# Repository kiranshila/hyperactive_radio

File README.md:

# Hyperactive//2026 Radio

Experimental real-time, long-range, high-quality, wireless digital audio for Hyperactive 2026.

## Audio quality

| Parameter | Value |
|-----------|-------|
| Codec | Opus (fixed-point) |
| Bitrate | 64 kbps |
| Channels | Stereo |
| Sample rate | 48 kHz |
| Frame size | 20 ms |
| Encoder complexity | 5 / 10 |
| ADC | PCM1808 (24-bit I2S) |

64 kbps stereo Opus at 48 kHz should be transparent for most program material — comparable to a good 128 kbps MP3, but with lower latency and better behaviour at the edges of the bitrate.
The fixed-point build removes float entirely; no performance penalty on Cortex-M33 which has a hardware FPU but where the float Opus path was benchmarked to be slower than fixed-point.

End-to-end latency is approximately one frame (20 ms) of algorithmic delay plus radio airtime (~1.6 ms at 100 kbps for a 160-byte packet) plus any playout buffer on the receiver.

## Radio

| Parameter | Value |
|-----------|-------|
| Radio IC | SX1276 |
| Band | 915 MHz (US ISM) |
| Modulation | GFSK |
| Air rate | 100 kbps |
| TX power | +20 dBm (100 mW) |
| Target range | ~300 m / ~1000 ft mixed indoor/outdoor |
| Link margin | ~18 dB at 100 kbps GFSK |

### Regulatory (FCC Part 15.247)

No frequency hopping required. Part 15.247 has two compliance paths — FHSS is one, but **digital modulation** is the other: fixed frequency, up to +30 dBm EIRP, with two constraints:

- **6 dB bandwidth ≥ 500 kHz** — requires high frequency deviation; at 100 kbps, ±200 kHz deviation gets you there (`BW_6dB ≈ 2 × f_dev + bit_rate`). Lower deviation (e.g. ±50 kHz) only yields ~200 kHz and does not qualify.
- **PSD ≤ 8 dBm in any 3 kHz band** — GFSK spectral peaks at ±f_dev must stay under this limit at the chosen TX power.

The exact deviation and power settings need to be verified against both constraints once the RF configuration is finalised. At +20 dBm with sufficiently high deviation the path is viable, but the numbers need to be checked.

### Packet structure

Each 20 ms Opus frame encodes to roughly 160 bytes at 64 kbps.
With ~10 bytes of framing (sequence number, network ID, CRC) the total packet is ~170 bytes, for an effective air rate of ~68 kbps — well within the 100 kbps channel.

## Performance

MCU runs at **270 MHz** (overclocked from the 150 MHz default; stable at stock 1.1 V).

Benchmarked on hardware against broadband LCG noise (worst case for Opus — no clear pitch, flat spectrum):

| Operation | Cycles (avg) | Time (avg) | Frame budget used |
|-----------|-------------|------------|-------------------|
| Opus encode, stereo, 64 kbps, 20 ms | 2,299,603 | 8.5 ms | **42.6%** |
| Opus decode, stereo, 64 kbps, 20 ms | 895,420 | 3.3 ms | **16.6%** |

Frame budget = 20 ms = 5,400,000 cycles at 270 MHz.

The encoder leaves 11.5 ms of headroom per frame for I2S DMA and SPI radio management.
The decoder uses only 16.6% of the frame, leaving ample margin for playout buffering and output DMA.

## Firmware architecture

Written in Rust (`no_std`, Embassy async runtime).

```
ha_radio/          # firmware binary (bench + main)
embedded-opus/     # safe Rust wrapper around libopus
opus-sys/          # raw FFI bindings; builds libopus via cc crate
```

`embedded-opus/build.rs` compiles a host-side C probe at build time to determine the exact encoder and decoder state sizes, so buffers are sized precisely without a runtime heap.

### Planned: dual-core pipeline

The encode headroom is comfortable at 270 MHz, but the dual-core split is still planned for clean separation of concerns once the ADC arrives:

- **Core 0** — I2S DMA capture, SX1276 SPI, radio management
- **Core 1** — Opus encode only

A pair of Embassy `Channel` queues (depth 2) connect the cores: PCM frames inbound, encoded packets outbound.

## Build

```sh
cargo build --release --bin ha_radio
cargo build --release --bin bench
```

Requires a Rust nightly toolchain and the `thumbv8m.main-none-eabihf` target (see `rust-toolchain.toml`).

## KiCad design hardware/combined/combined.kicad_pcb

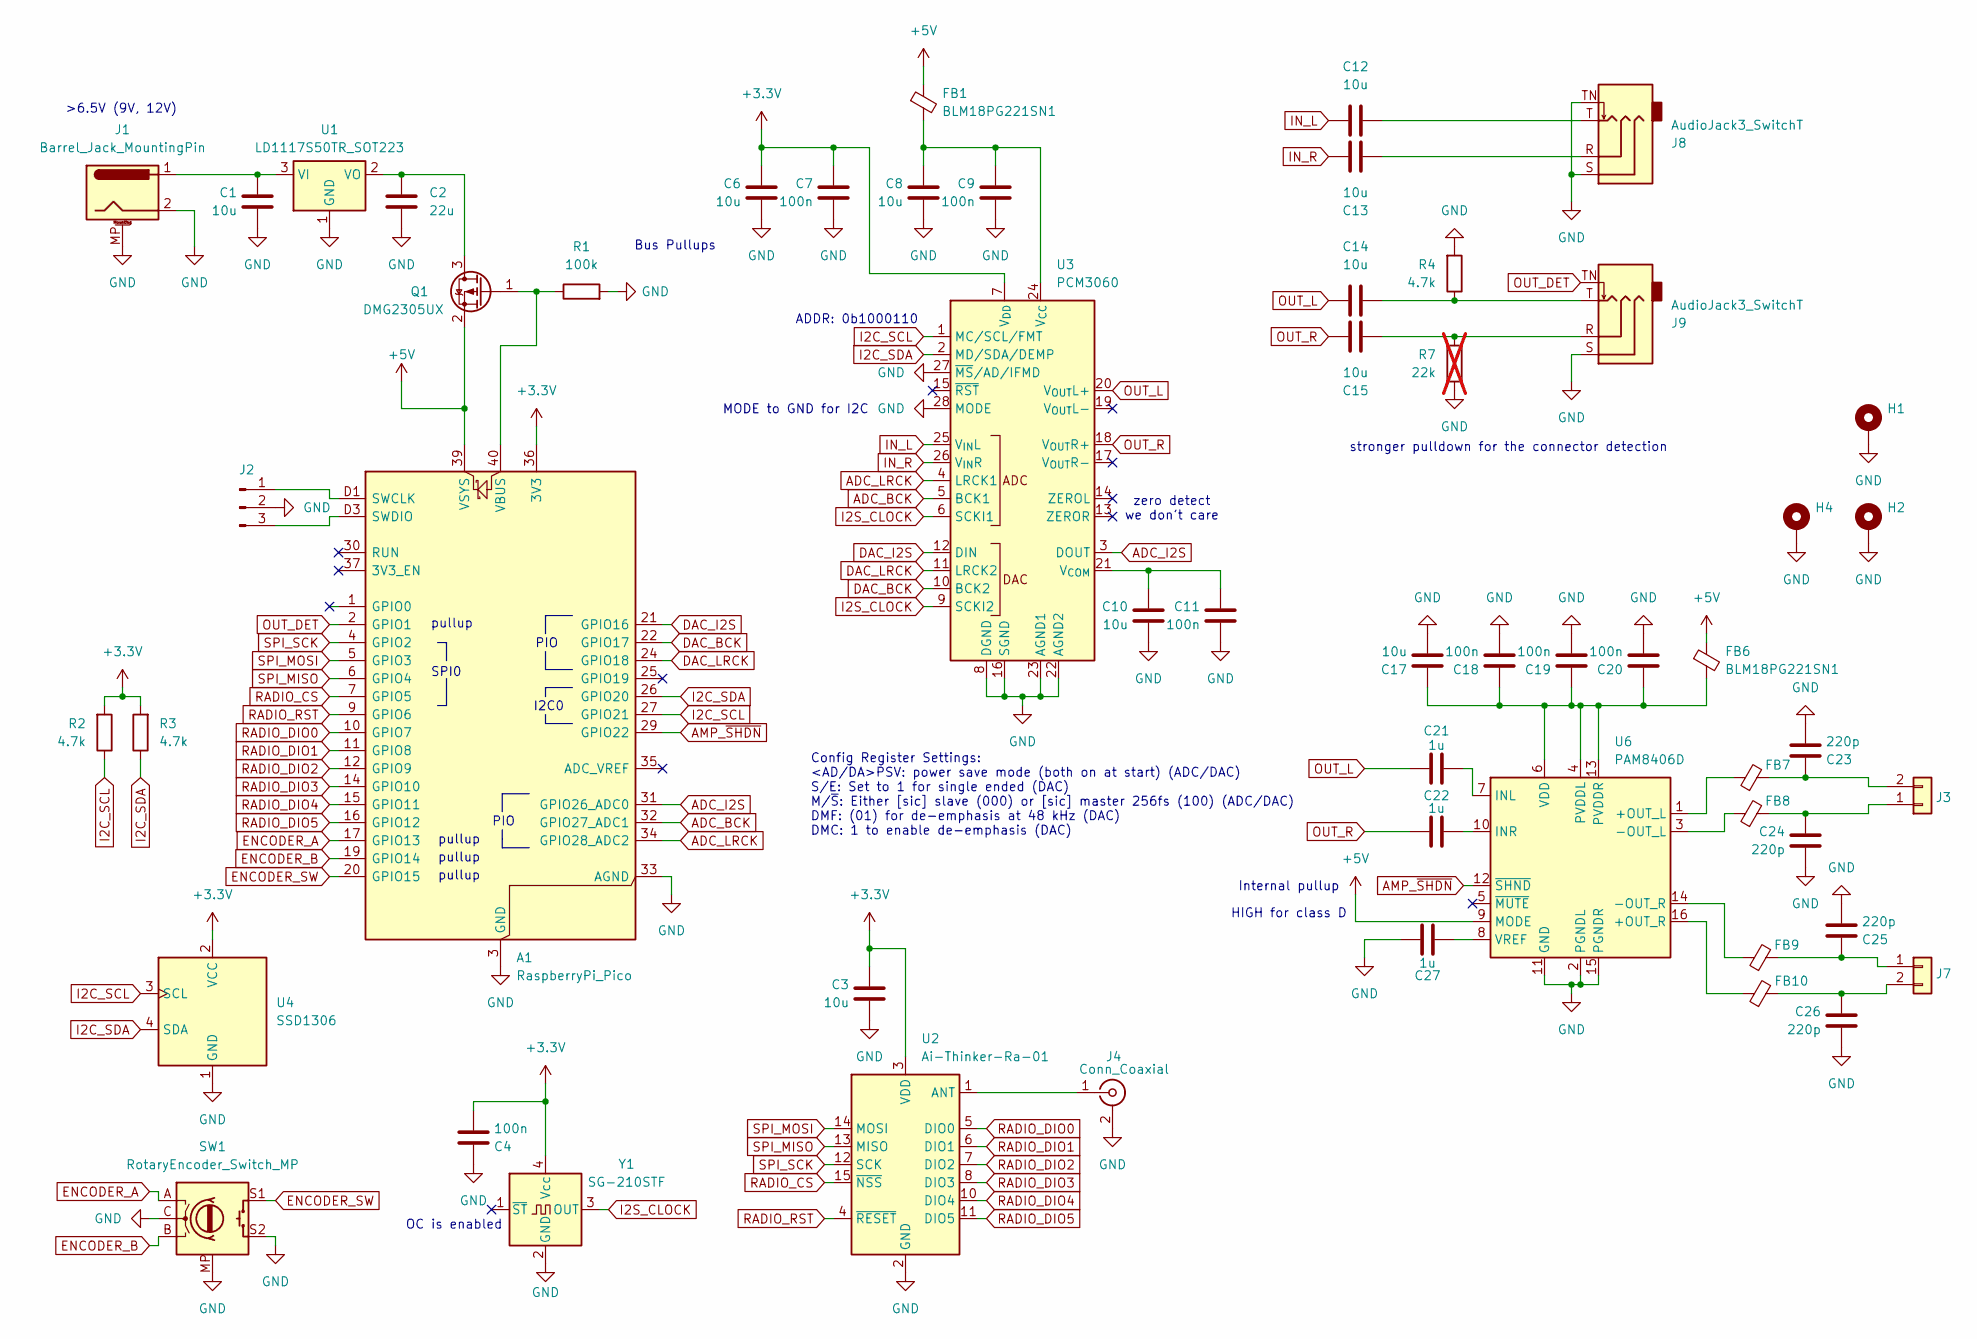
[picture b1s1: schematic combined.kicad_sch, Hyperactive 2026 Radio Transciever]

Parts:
A1: RaspberryPi_Pico; RaspberryPi_Pico_SMD_HandSolder; LCSC C41407547
C1, C3, C6, C8, C10, C12, C13, C14, C15, C17: 10u; C_0805_2012Metric; MPN CL21A106KOQNNNG
C2: 22u; C_0805_2012Metric; MPN GRM21BR61A226ME51L
C4, C7, C9, C11, C18, C19, C20: 100n; C_0805_2012Metric; MPN 0805ZD104KAT2A
C21, C22, C27: 1u; C_0805_2012Metric; MPN 0805X105K160CT
C23, C24, C25, C26: 220p; C_0603_1608Metric; MPN C0603C221J1HACAUTO
FB1, FB6, FB7, FB8, FB9, FB10: BLM18PG221SN1; L_0603_1608Metric; MPN BLM18PG221SN1; LCSC C80165
H1, H2, H4: MountingHole_Pad; MountingHole_3.2mm_M3_DIN965_Pad_TopBottom
J1: Barrel_Jack_MountingPin; BarrelJack_Horizontal
J2: Conn_01x03_Pin; PinHeader_1x03_P2.54mm_Vertical
J3, J7: Conn_01x02; PinHeader_1x02_P2.54mm_Vertical
J4: Conn_Coaxial; SMA_Samtec_SMA-J-P-H-ST-EM1_EdgeMount; LCSC C496550
J8, J9: AudioJack3_SwitchT; Jack_3.5mm_CUI_SJ-3524-SMT_Horizontal; MPN SJ-3524-SMT-TR; LCSC C20182907
Q1: DMG2305UX; SOT-23; LCSC C150470
R1: 100k; R_0805_2012Metric; MPN RG2012P-104-B-T5
R2, R3, R4: 4.7k; R_0805_2012Metric; MPN RG2012P-472-D-T5
R7: 22k; R_0805_2012Metric; MPN RG2012P-223-B-T5; not fitted
SW1: RotaryEncoder_Switch_MP; RotaryEncoder_Alps_EC11E-Switch_Vertical_H20mm; MPN EC11E09244BS; LCSC C470742
U1: LD1117S50TR_SOT223; SOT-223-3_TabPin2; LCSC C347230
U2: Ai-Thinker-Ra-01; Ai-Thinker-Ra-01-LoRa; LCSC C503593
U3: PCM3060; TSSOP-28_4.4x9.7mm_P0.65mm; MPN PCM3060PWR; LCSC C2651841
U4: SSD1306; SSD1306_0.96_Oled
U6: PAM8406D; SOIC-16_3.9x9.9mm_P1.27mm; MPN PAM8406DR; LCSC C86270
Y1: SG-210STF; Oscillator_SMD_SeikoEpson_SG210-4Pin_2.5x2.0mm; MPN X1G0041710019; LCSC C255992

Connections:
+3.3V: A1.36 (3V3), C3.2, C4.1, C6.2, C7.2, R2.2, R3.2, U2.3 (VDD), U3.7 (V_{DD}), U4.2 (VCC), Y1.4 (Vcc)
+5V: A1.39 (VSYS), FB1.1, FB6.1, Q1.2 (S), U6.9 (MODE)
ADC_BCK: A1.32 (GPIO27_ADC1), U3.5 (BCK1)
ADC_I2S: A1.31 (GPIO26_ADC0), U3.3 (DOUT)
ADC_LRCK: A1.34 (GPIO28_ADC2), U3.4 (LRCK1)
AMP_~SHDN: A1.29 (GPIO22), U6.12 (~SHND)
DAC_BCK: A1.22 (GPIO17), U3.10 (BCK2)
DAC_I2S: A1.21 (GPIO16), U3.12 (DIN)
DAC_LRCK: A1.24 (GPIO18), U3.11 (LRCK2)
ENCODER_A: A1.17 (GPIO13), SW1.A
ENCODER_B: A1.19 (GPIO14), SW1.B
ENCODER_SW: A1.20 (GPIO15), SW1.S1
GND: A1.3 (GND), A1.8 (GND), A1.13 (GND), A1.18 (GND), A1.23 (GND), A1.28 (GND), A1.33 (AGND), A1.38 (GND), A1.D2 (GND), C1.1, C2.2, C3.1, C4.2, C6.1, C7.1, C8.1, C9.1, C10.1, C11.1, C17.1, C18.1, C19.1, C20.1, C23.1, C24.1, C25.1, C26.1, C27.2, H1.1 (1_1), H2.1 (1_1), H4.1 (1_1), J1.2, J1.MP (MountPin), J2.2, J4.2 (Ext), J8.S, J8.TN, J9.S, R1.2, R4.2, R7.1, SW1.C, SW1.MP, SW1.S2, U1.1 (GND), U2.2 (GND), U2.9 (GND), U2.16 (GND), U3.8 (DGND), U3.16 (SGND), U3.22 (AGND2), U3.23 (AGND1), U3.27 (~MS/AD/IFMD), U3.28 (MODE), U4.1 (GND), U6.2 (PGNDL), U6.11 (GND), U6.15 (PGNDR), Y1.2 (GND)
I2C_SCL: A1.27 (GPIO21), R2.1, U3.1 (MC/SCL/FMT), U4.3 (SCL)
I2C_SDA: A1.26 (GPIO20), R3.1, U3.2 (MD/SDA/DEMP), U4.4 (SDA)
I2S_CLOCK: U3.6 (SCKI1), U3.9 (SCKI2), Y1.3 (OUT)
IN_L: C12.1, U3.25 (V_{IN}L)
IN_R: C13.1, U3.26 (V_{IN}R)
unnamed: A1.D1 (SWCLK), J2.1
unnamed: A1.D3 (SWDIO), J2.3
unnamed: A1.40 (VBUS), Q1.1 (G), R1.1
unnamed: C12.2, J8.T
unnamed: C13.2, J8.R
unnamed: C14.2, J9.T, R4.1
unnamed: C15.2, J9.R, R7.2
unnamed: C24.2, FB8.2, J3.1
unnamed: C23.2, FB7.2, J3.2
unnamed: J4.1 (In), U2.1 (ANT)
unnamed: C25.2, FB9.2, J7.1
unnamed: C26.2, FB10.2, J7.2
unnamed: C2.1, Q1.3 (D), U1.2 (VO)
unnamed: C1.2, J1.1, U1.3 (VI)
unnamed: C8.2, C9.2, FB1.2, U3.24 (V_{CC})
unnamed: C10.2, C11.2, U3.21 (V_{COM})
unnamed: FB7.1, U6.1 (+OUT_L)
unnamed: FB10.1, U6.16 (+OUT_R)
unnamed: FB8.1, U6.3 (-OUT_L)
unnamed: FB9.1, U6.14 (-OUT_R)
unnamed: C21.1, U6.7 (INL)
unnamed: C22.1, U6.10 (INR)
unnamed: C17.2, C18.2, C19.2, C20.2, FB6.2, U6.4 (PVDDL), U6.6 (VDD), U6.13 (PVDDR)
unnamed: C27.1, U6.8 (VREF)
OUT_DET: A1.2 (GPIO1), J9.TN
OUT_L: C14.1, C21.2, U3.20 (V_{OUT}L+)
OUT_R: C15.1, C22.2, U3.18 (V_{OUT}R+)
RADIO_CS: A1.7 (GPIO5), U2.15 (~NSS)
RADIO_DIO0: A1.10 (GPIO7), U2.5 (DIO0)
RADIO_DIO1: A1.11 (GPIO8), U2.6 (DIO1)
RADIO_DIO2: A1.12 (GPIO9), U2.7 (DIO2)
RADIO_DIO3: A1.14 (GPIO10), U2.8 (DIO3)
RADIO_DIO4: A1.15 (GPIO11), U2.10 (DIO4)
RADIO_DIO5: A1.16 (GPIO12), U2.11 (DIO5)
RADIO_RST: A1.9 (GPIO6), U2.4 (~RESET)
SPI_MISO: A1.6 (GPIO4), U2.13 (MISO)
SPI_MOSI: A1.5 (GPIO3), U2.14 (MOSI)
SPI_SCK: A1.4 (GPIO2), U2.12 (SCK)

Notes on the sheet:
MODE to GND for I2C
I2C0
stronger pulldown for the connector detection
HIGH for class D
PIO
Internal pullup
OC is enabled
pullup
Bus Pullups
ADDR: 0b1000110
zero detect we don't care
>6.5V (9V, 12V)
Config Register Settings: <AD/DA>PSV: power save mode (both on at start) (ADC/DAC) S/E: Set to 1 for single ended (DAC) M/~{S}: Either [sic] slave (000) or [sic] master 256fs (100) (ADC/DAC) DMF: (01) for de-emphasis at 48 kHz (DAC) DMC: 1 to enable de-emphasis (DAC)
SPI0

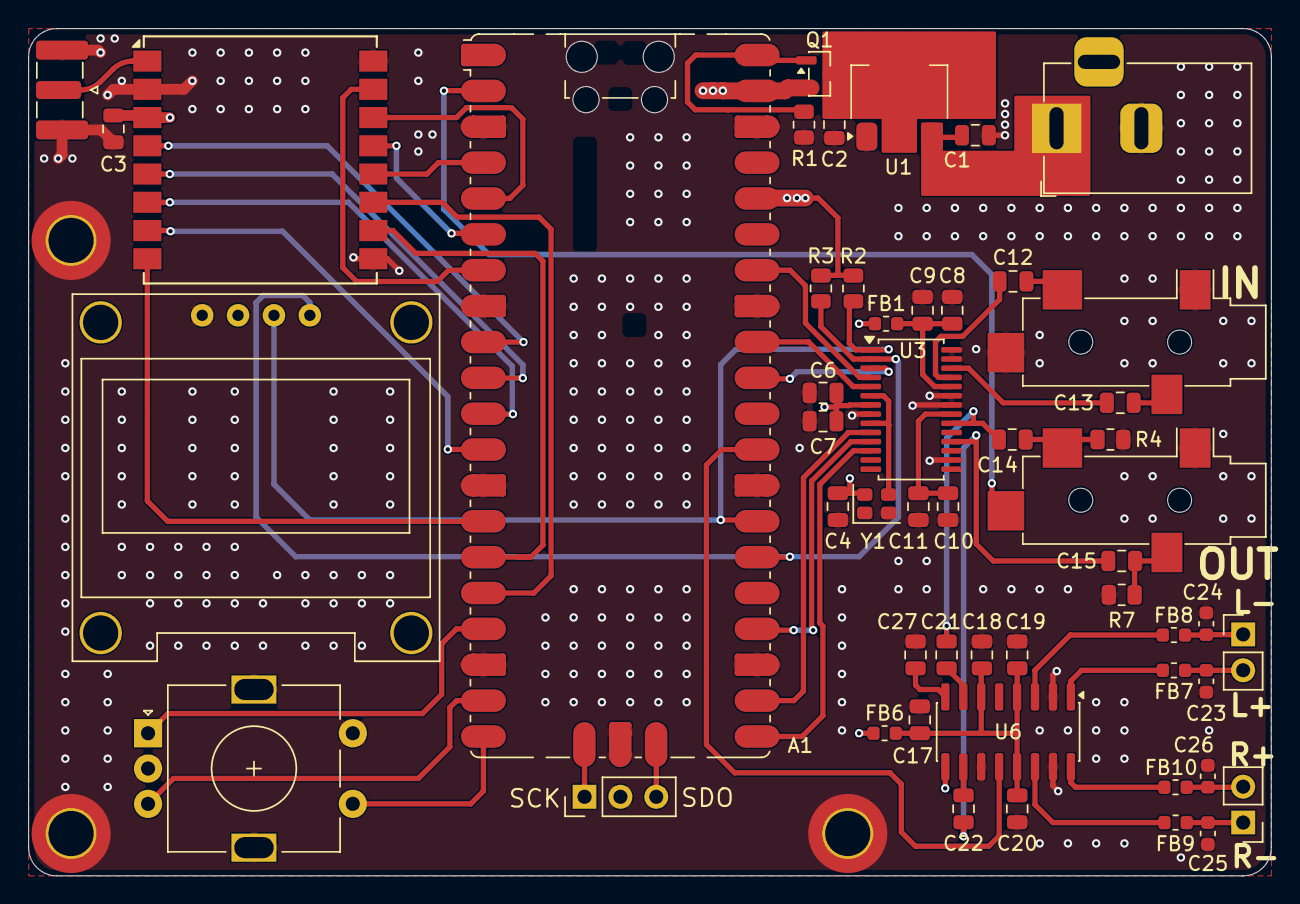
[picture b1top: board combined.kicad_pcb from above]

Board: 4 copper layers, 88.0 x 60.0 mm, 55 parts (0 on the bottom side), 56 nets.

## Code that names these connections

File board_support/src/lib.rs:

//! All the boilerplate for initializing the board

#![no_std]
#![no_main]

pub mod consts;
pub mod encoder;
pub mod i2s;

use crate::{
    encoder::Encoder,
    i2s::{I2sInput, I2sOutput, PioI2sInProgram, PioI2sOutProgram},
};
use core::marker::PhantomData;
use embassy_embedded_hal::shared_bus::asynch::{i2c::I2cDevice, spi::SpiDevice};
use embassy_rp::{
    Peri,
    clocks::ClockConfig,
    dma::{ChannelInstance, InterruptHandler as DmaInterruptHandler},
    gpio::{Input, Level, Output, Pull},
    i2c::{
        Async as I2cAsync, Config as I2cConfig, I2c, Instance as I2cInstance,
        InterruptHandler as I2cInterruptHandler,
    },
    interrupt::typelevel::Binding,
    peripherals::{CORE1, DMA_CH0, DMA_CH1, DMA_CH2, DMA_CH3, I2C0, PIO0, PIO1, SPI0},
    pio::{Instance as PioInstance, InterruptHandler as PioInterruptHandler, Pio},
    pwm::Pwm,
    spi::{Async as SpiAsync, Config as SpiConfig, Spi},
};
use embassy_sync::{blocking_mutex::raw::CriticalSectionRawMutex, mutex::Mutex};
use pcm3060::Pcm3060;
use static_cell::StaticCell;
use sx127x::Sx127x;

type I2c0 = I2c<'static, I2C0, I2cAsync>;
type I2c0Bus = Mutex<CriticalSectionRawMutex, I2c0>;
type I2c0Device = I2cDevice<'static, CriticalSectionRawMutex, I2c0>;
type Spi0 = Spi<'static, SPI0, SpiAsync>;
type Spi0Bus = Mutex<CriticalSectionRawMutex, Spi0>;
type Spi0Device = SpiDevice<'static, CriticalSectionRawMutex, Spi0, Output<'static>>;

pub type I2sInputPio = I2sInput<'static, PIO0, 0>;
pub type I2sOutputPio = I2sOutput<'static, PIO0, 1>;
pub type VolumeEncoderPio = Encoder<'static, PIO1, 0, 200, 255>;
pub type Pcm3060Board = Pcm3060<I2c0Device>;
pub type Sx127xBoard = Sx127x<Spi0Device>;

const CLOCK_FREQ_HZ: u32 = 240_000_000;

static I2C0_BUS: StaticCell<I2c0Bus> = StaticCell::new();

/// Represents all the peripherals and pins as wired on the production board
pub struct Board<IRQS> {
    /// Headphone/Line Out Detect
    /// Active-low when a plug is inserted.
    pub out_det: Input<'static>,

    /// Radio GPIO
    pub radio_rst: Output<'static>,
    pub radio_d0: Input<'static>,
    pub radio_d1: Input<'static>,
    pub radio_d2: Input<'static>,
    pub radio_d3: Input<'static>,
    pub radio_d4: Input<'static>,
    pub radio_d5: Input<'static>,

    /// Rotary Encoder
    // pub encoder_a: Peri<'static, PIN_13>,
    // pub encoder_b: Peri<'static, PIN_14>,
    // pub encoder_sw: Peri<'static, PIN_15>,

    /// Audio Codec Software Control
    pub codec: Pcm3060Board,

    /// Audio amp shutdown pin
    pub amp_nshdn: Output<'static>,

    /// I2S PIO Programs
    pub i2s_out: I2sOutputPio,
    pub i2s_in: I2sInputPio,

    /// Radio
    pub radio: Sx127xBoard,

    /// IRQ Marker
    irqs: PhantomData<IRQS>,

    /// Core 1
    pub core_1: Peri<'static, CORE1>,

    /// Rotary encoder
    pub volume_knob: VolumeEncoderPio,

    // LEDs
    pub led_1: Pwm<'static>,
    pub led_2: Pwm<'static>,
}

impl<IRQS> Board<IRQS>
where
    IRQS: Binding<<I2C0 as I2cInstance>::Interrupt, I2cInterruptHandler<I2C0>>
        + Binding<<PIO0 as PioInstance>::Interrupt, PioInterruptHandler<PIO0>>
        + Binding<<DMA_CH0 as ChannelInstance>::Interrupt, DmaInterruptHandler<DMA_CH0>>
        + Binding<<DMA_CH1 as ChannelInstance>::Interrupt, DmaInterruptHandler<DMA_CH1>>
        + Binding<<DMA_CH2 as ChannelInstance>::Interrupt, DmaInterruptHandler<DMA_CH2>>
        + Binding<<DMA_CH3 as ChannelInstance>::Interrupt, DmaInterruptHandler<DMA_CH3>>
        + Binding<<PIO1 as PioInstance>::Interrupt, PioInterruptHandler<PIO1>>
        + 'static,
{
    pub fn new(mut config: embassy_rp::config::Config, irqs: IRQS) -> Self {
        config.clocks = ClockConfig::system_freq(CLOCK_FREQ_HZ).unwrap();
        let p = embassy_rp::init(config);

        // Amp shutdown pin
        let amp_nshdn = Output::new(p.PIN_22, Level::Low);

        // Setup I2C
        let mut i2c_cfg = I2cConfig::default();
        i2c_cfg.frequency = 400_000;
        let i2c = I2c::new_async(p.I2C0, p.PIN_21, p.PIN_20, irqs, i2c_cfg);
        let i2c_bus = I2C0_BUS.init(Mutex::new(i2c));

        // Setup Codec
        let codec = Pcm3060::new(I2cDevice::new(i2c_bus), false);

        // Setup I2S
        let Pio {
            mut common,
            sm0,
            sm1,
            ..
        } = Pio::new(p.PIO0, irqs);

        let i2s_in_prg = PioI2sInProgram::new(&mut common);
        let i2s_in = I2sInput::new(
            &mut common,
            sm0,
            p.DMA_CH0,
            irqs,
            p.PIN_26,
            p.PIN_27,
            p.PIN_28,
            &i2s_in_prg,
        );

        let i2s_out_prg = PioI2sOutProgram::new(&mut common);
        let i2s_out = I2sOutput::new(
            &mut common,
            sm1,
            p.DMA_CH1,
            irqs,
            p.PIN_16,
            p.PIN_17,
            p.PIN_18,
            &i2s_out_prg,
        );

        // Output jack detection
        let out_det = Input::new(p.PIN_1, Pull::Up);

        // SPI for radio
        let mut config = SpiConfig::default();
        config.frequency = 10_000_000;
        let spi = Spi::new(
            p.SPI0, p.PIN_2, p.PIN_3, p.PIN_4, p.DMA_CH2, p.DMA_CH3, irqs, config,
        );
        static SPI_BUS: StaticCell<Spi0Bus> = StaticCell::new();
        let spi_bus = SPI_BUS.init(Mutex::new(spi));
        let cs = Output::new(p.PIN_5, Level::High);
        let spi_dev = SpiDevice::new(spi_bus, cs);

        // Radio
        let radio = Sx127x::new(spi_dev);

        // Other GPIO
        let radio_rst = Output::new(p.PIN_6, Level::High);
        let radio_d0 = Input::new(p.PIN_7, Pull::Down);
        let radio_d1 = Input::new(p.PIN_8, Pull::Down);
        let radio_d2 = Input::new(p.PIN_9, Pull::Down);
        let radio_d3 = Input::new(p.PIN_10, Pull::Down);
        let radio_d4 = Input::new(p.PIN_11, Pull::Down);
        let radio_d5 = Input::new(p.PIN_12, Pull::Down);

        // Setup rotary encoder
        let Pio {
            mut common, sm0, ..
        } = Pio::new(p.PIO1, irqs);

        let encoder = VolumeEncoderPio::new(&mut common, sm0, p.PIN_13, p.PIN_14);

        let led_1 = Pwm::new_output_a(p.PWM_SLICE0, p.PIN_0, Default::default());
        let led_2 = Pwm::new_output_b(p.PWM_SLICE1, p.PIN_19, Default::default());

        Self {
            codec,
            amp_nshdn,
            out_det,
            radio,
            i2s_out,
            i2s_in,
            irqs: PhantomData,
            radio_rst,
            radio_d0,
            radio_d1,
            radio_d2,
            radio_d3,
            radio_d4,
            radio_d5,
            core_1: p.CORE1,
            volume_knob: encoder,
            led_1,
            led_2,
        }
    }
}

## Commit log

2026-03-18 feat: first commit
2026-03-18 feat: remove unsafe, overclock to 270 MHz, add a few more DSP hints
2026-03-18 feat: README
2026-03-18 chore: nits
2026-03-18 chore: README fixes
2026-03-28 feat: first pass at everything working
2026-03-28 feat: first go at TX hardware design
2026-04-03 feat: detect CRC errors
    without disabling CRC auto-clear, we appeared to pass invalid packets...
    straight to whoever was reading data from the radio, which (since we're
    receiving packets longer than the FIFO) meant they got a packet that was
    invalid /and/ too short. disabling auto-clear makes the radio behave as
    expected by the rest of the code.
2026-04-03 feat: restart on rx hang, handle CRCs
    occasionally, the receiver will hang. since we don't want our friends
    left in the lurch, music-wise, we should probably auto-restrat after
    timing out too many times.
    also, notice when CRC errors occur and tell opus to figure it out.
2026-04-03 trigger PLC on too-large packets
2026-04-03 count CRC errors
2026-04-07 feat: combined hardware
2026-04-07 feat: oled model
2026-04-23 feat: support for final board design
2026-04-23 feat: nausicaa tweaks to RX
2026-04-29 [broken] switch to master mode on the DAC side
    basically, the bug as far as i can tell was: we were asserting BCK and
    LRCK for the DAC input, but those signals don't stay synchronized with
    the crystal that's driving the DAC's SCK, so every so often (~200 ms
    empirically) the DAC detects a desync, outputs "undefined data" for a
    bit, then resets to 0.5 of full range and starts running again.
    the fix is to use the DAC in master mode, and read BCK/LRCK on the 2350,
2026-04-29 run in/out in the same sm
2026-04-29 [fixed] set DAC to 256 Fs
    no more clicking!
2026-04-29 add two comments
2026-04-29 implement volume control
    this commit:
    - adds an encoder driver (which doesn't use the switch but we can do
    that later)
    - multiplies the incoming audio by that encoder value
    we might want to think a bit harder about more erudite volume control
    mechanisms than "just fkin multiply em" but this certainly works.
2026-04-29 bit-shifting volume control, implement on rx
2026-04-29 hardware volume control, much saner
2026-05-01 chore: merge irqs
2026-05-01 feat: add output LEDs
2026-05-01 feat: add FEC to opus
2026-05-01 chore: bump output power to 20 dBm
2026-05-02 chore: fixup led
2026-05-02 chore: lower transmit to 17
2026-05-02 feat: add max payload size to radio config
2026-05-02 chore: reduce timeout
